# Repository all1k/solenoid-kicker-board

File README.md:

# Solenoid Kicker Board

Electronic design for a solenoid based kicker actuator on a RoboCup MSL based Robots

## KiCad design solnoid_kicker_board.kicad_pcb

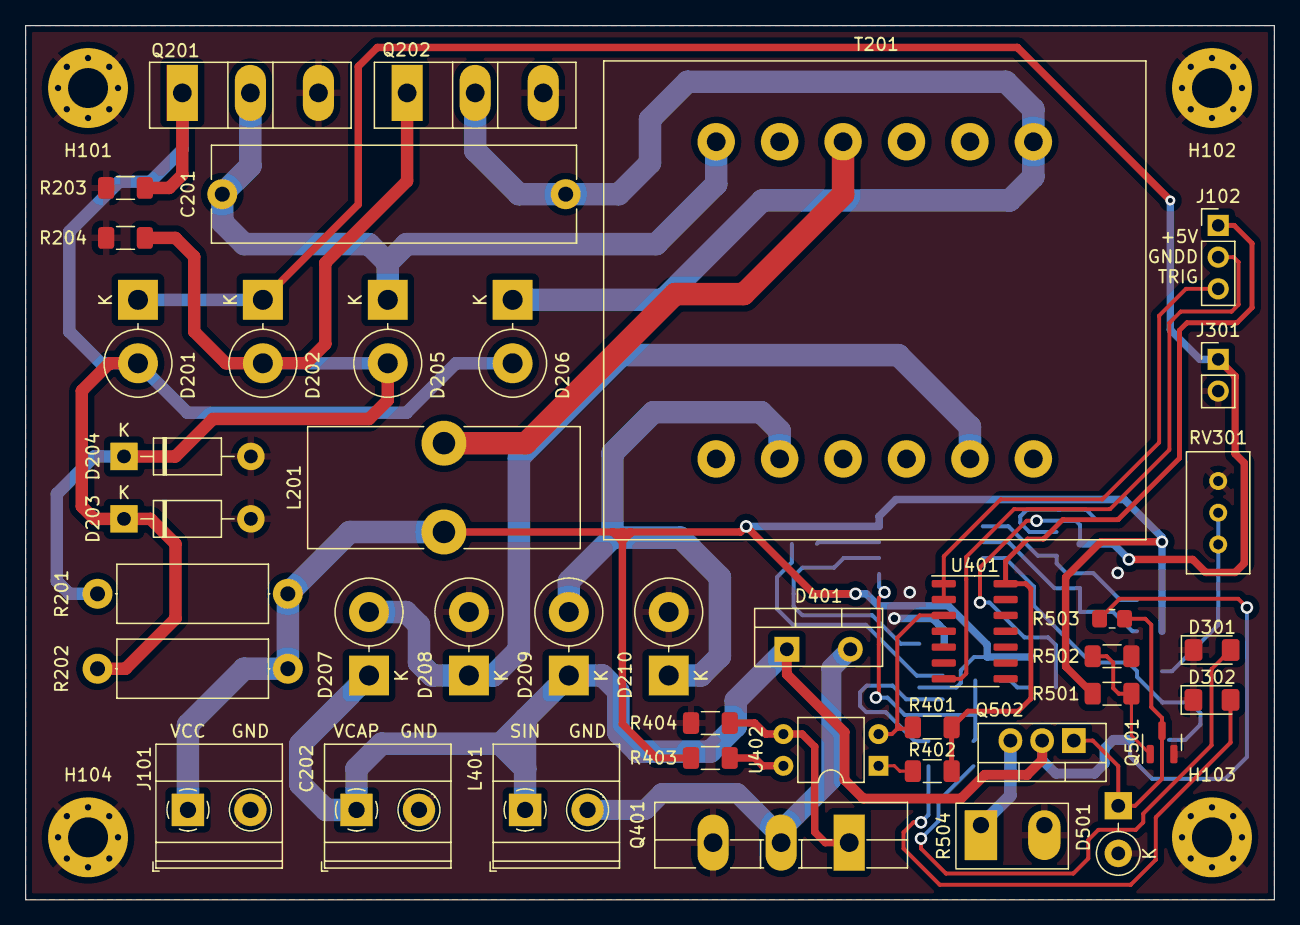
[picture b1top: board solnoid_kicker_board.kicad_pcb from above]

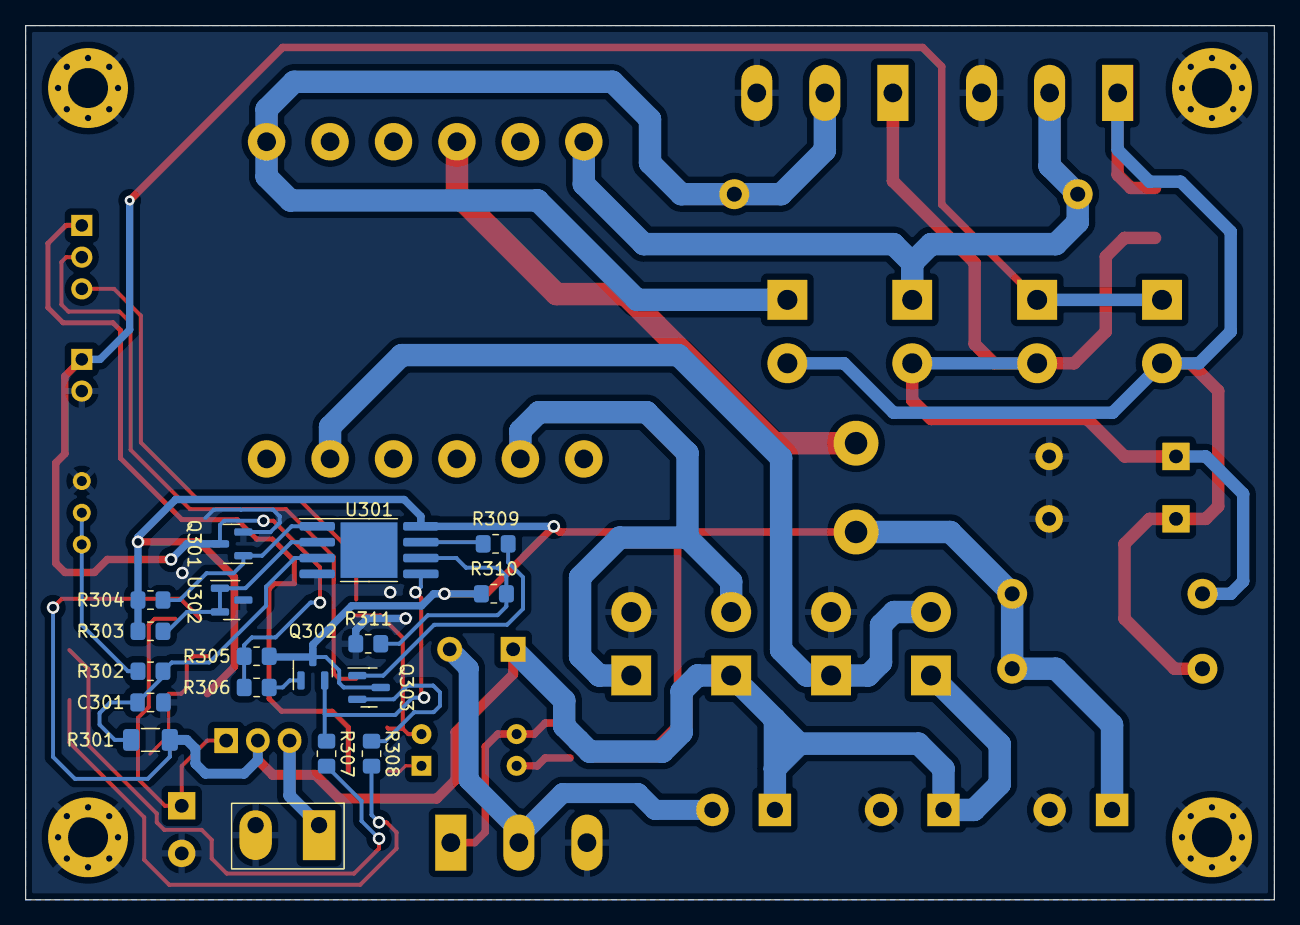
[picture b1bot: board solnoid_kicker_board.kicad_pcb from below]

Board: 2 copper layers, 100.0 x 70.0 mm, 63 parts (17 on the bottom side), 34 nets.

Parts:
C201: 4.2µF 400V; C_Rect_L29.0mm_W7.6mm_P27.50mm_MKT
C202: 4700µF 450V; TerminalBlock_Phoenix_MKDS-1,5-2_1x02_P5.00mm_Horizontal
C301: 1nF; C_0805_2012Metric_Pad1.18x1.45mm_HandSolder
D201, D202, D205, D206, D207, D208, D209, D210: FR307; D_DO-201AD_P5.08mm_Vertical_KathodeUp
D203, D204: 1N47xxA 12V; D_DO-41_SOD81_P10.16mm_Horizontal
D301, D302: LED; LED_1206_3216Metric_Pad1.42x1.75mm_HandSolder
D401: RHRP3060; TO-220-2_Vertical
D501: 1N47xxA 12V; D_DO-41_SOD81_P3.81mm_Vertical_KathodeUp
H101, H102, H103, H104: MountingHole_Pad; MountingHole_3.2mm_M3_Pad_Via
J101: Screw_Terminal_01x02; TerminalBlock_Phoenix_MKDS-1,5-2_1x02_P5.00mm_Horizontal
J102: Conn_01x03; PinHeader_1x03_P2.54mm_Vertical
J301: Conn_01x02; PinHeader_1x02_P2.54mm_Vertical
L201: L_Iron; L_Toroid_Vertical_L21.6mm_W9.5mm_P7.11mm_Pulse_C
L401: Solenoid; TerminalBlock_Phoenix_MKDS-1,5-2_1x02_P5.00mm_Horizontal
Q201, Q202: IRFP250; TO-247-3_Vertical
Q301, Q501: MMBT3904; SOT-23
Q302, Q303: MMBT3906; SOT-23
Q401: FGL40N120; TO-264-3_Vertical
Q502: IRF840; TO-220-3_Vertical
R201, R202: 470Ω 2W; R_Axial_DIN0414_L11.9mm_D4.5mm_P15.24mm_Horizontal
R203, R204, R401, R403, R404: 10kΩ; R_1206_3216Metric_Pad1.30x1.75mm_HandSolder
R301: 1MΩ; R_1206_3216Metric_Pad1.30x1.75mm_HandSolder
R302: 5.6kΩ; R_0805_2012Metric_Pad1.20x1.40mm_HandSolder
R303: 2.2kΩ; R_0805_2012Metric_Pad1.20x1.40mm_HandSolder
R304, R307, R308: 1kΩ; R_0805_2012Metric_Pad1.20x1.40mm_HandSolder
R305: 18kΩ; R_0805_2012Metric_Pad1.20x1.40mm_HandSolder
R306, R309: 680Ω; R_0805_2012Metric_Pad1.20x1.40mm_HandSolder
R310, R311: 15kΩ; R_0805_2012Metric_Pad1.20x1.40mm_HandSolder
R402: 330Ω; R_1206_3216Metric_Pad1.30x1.75mm_HandSolder
R501, R502: 1kΩ; R_1206_3216Metric_Pad1.30x1.75mm_HandSolder
R503: 470kΩ; R_0805_2012Metric_Pad1.20x1.40mm_HandSolder
R504: 56kΩ 5W; TerminalBlock_Phoenix_MKDS-1,5-2-5.08_1x02_P5.08mm_Horizont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
RV301: 1kΩ; Potentiometer_Bourns_3296W_Vertical
T201: Transformer_SP_1S; Transformer_37x44
U301: LM393; SOP-8-1EP_4.57x4.57mm_P1.27mm_EP4.57x4.45mm
U302: TL431DBZ; SOT-23
U401: 74HC00; SO-14_3.9x8.65mm_P1.27mm
U402: PC817; DIP-4_W7.62mm

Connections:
+5V: J102.1, R401.1, R402.1, U401.14 (VCC)
+12V: J101.1, L201.1, Q302.3 (C), Q303.3 (C), R201.1, R202.1, R303.1, R304.1, R305.1, R310.1, R403.1, R501.1, U301.8 (V+)
/Discharge Circuit/VCAP_IN: C202.1, D207.1 (K), D209.1 (K), D401.1 (Cathode), L401.1, Q502.2 (D), R301.1, R503.1
/Flyback_Driver/ENABLE: D201.1 (K), D202.1 (K), J301.1, Q301.3 (C), R305.2, R306.2
/Trigger Circuit/SNET: D401.2 (Anode), L401.2, Q401.2 (C)
/Trigger Circuit/TRIGG: J102.3, U401.1, U401.2
GNDD: J102.2, U401.7 (GND)
GNDREF: C202.2, C301.2, D203.2 (A), D204.2 (A), D208.2 (A), D210.2 (A), D301.1 (K), D302.1 (K), D501.2 (A), H101.1, H102.1, H103.1, H104.1, J101.2, J301.2, Q201.3 (S), Q202.3 (S), Q301.2 (E), Q401.3 (E), Q501.2 (E), R203.2, R204.1, R311.2, R404.2, R502.2, R504.2, RV301.3, U301.4 (V-), U302.3 (A)
unnamed: C201.1, D205.1 (K), Q201.2 (D), T201.1 (PR1)
unnamed: C201.2, D206.1 (K), Q202.2 (D), T201.3 (PR2)
unnamed: C301.1, R301.2, R302.1, U301.3 (+)
unnamed: D201.2 (A), D203.1 (K), D206.2 (A), Q201.1 (G), R202.2, R203.1
unnamed: D202.2 (A), D204.1 (K), D205.2 (A), Q202.1 (G), R201.2, R204.2
unnamed: D207.2 (A), D208.1 (K), T201.5 (S2)
unnamed: D209.2 (A), D210.1 (K), T201.4 (S1)
unnamed: D301.2 (A), R307.2
unnamed: D302.2 (A), R308.2
unnamed: D501.1 (K), Q501.3 (C), Q502.1 (G), R503.2
unnamed: L201.2, T201.2 (PM)
unnamed: Q301.1 (B), R304.2, U301.1
unnamed: Q302.1 (B), R306.1
unnamed: Q302.2 (E), R307.1, U301.5 (+)
unnamed: Q303.1 (B), R309.2
unnamed: Q303.2 (E), R308.1
unnamed: Q401.1 (G), R404.1, U402.3
unnamed: Q501.1 (B), R501.2, R502.1
unnamed: Q502.3 (S), R504.1
unnamed: R302.2, RV301.1, RV301.2
unnamed: R303.2, U301.2 (-), U302.1 (K), U302.2 (REF)
unnamed: R309.1, U301.7
unnamed: R310.2, R311.1, U301.6 (_)
unnamed: R401.2, U401.3, U402.2
unnamed: R402.2, U402.1
unnamed: R403.2, U402.4

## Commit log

2022-12-09 Cropped preview image
